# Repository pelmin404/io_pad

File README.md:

# io_pad
A macropad that can act as a push button hub

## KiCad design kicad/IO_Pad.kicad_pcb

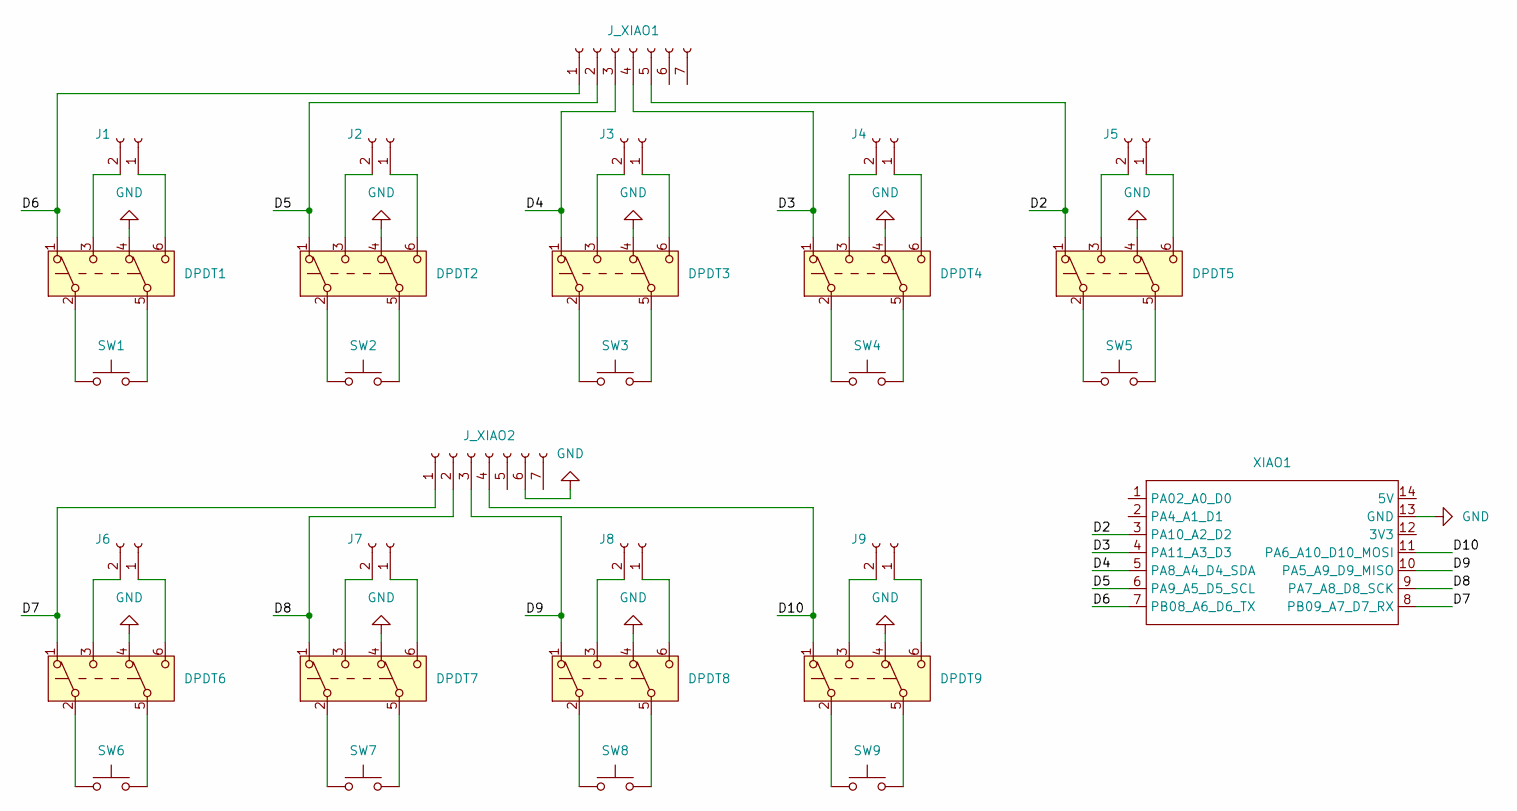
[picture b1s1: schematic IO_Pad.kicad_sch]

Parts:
DPDT1, DPDT2, DPDT3, DPDT4, DPDT5, DPDT6, DPDT7, DPDT8, DPDT9: SW_Push_DPDT; SWITCH_011CQN
J1, J2, J3, J4, J5, J6, J7, J8, J9: Conn_01x02_Socket; PinSocket_1x02_P2.54mm_Vertical
J_XIAO1, J_XIAO2: Conn_01x07_Socket; PinSocket_1x07_P2.54mm_Vertical
SW1, SW2, SW3, SW4, SW5, SW6, SW7, SW8, SW9: SW_Push; MX-Solderable-1U
XIAO1: MOUDLE-SEEEDUINO-XIAO

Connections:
/D2: DPDT5.1 (A), J_XIAO1.5, XIAO1.3 (PA10_A2_D2)
/D3: DPDT4.1 (A), J_XIAO1.4, XIAO1.4 (PA11_A3_D3)
/D4: DPDT3.1 (A), J_XIAO1.3, XIAO1.5 (PA8_A4_D4_SDA)
/D5: DPDT2.1 (A), J_XIAO1.2, XIAO1.6 (PA9_A5_D5_SCL)
/D6: DPDT1.1 (A), J_XIAO1.1, XIAO1.7 (PB08_A6_D6_TX)
/D7: DPDT6.1 (A), J_XIAO2.1, XIAO1.8 (PB09_A7_D7_RX)
/D8: DPDT7.1 (A), J_XIAO2.2, XIAO1.9 (PA7_A8_D8_SCK)
/D9: DPDT8.1 (A), J_XIAO2.3, XIAO1.10 (PA5_A9_D9_MISO)
/D10: DPDT9.1 (A), J_XIAO2.4, XIAO1.11 (PA6_A10_D10_MOSI)
GND: DPDT1.4 (A), DPDT2.4 (A), DPDT3.4 (A), DPDT4.4 (A), DPDT5.4 (A), DPDT6.4 (A), DPDT7.4 (A), DPDT8.4 (A), DPDT9.4 (A), J_XIAO2.6, XIAO1.13 (GND)
unnamed: DPDT1.2 (B), SW1.1
unnamed: DPDT1.5 (B), SW1.2
unnamed: DPDT2.2 (B), SW2.1
unnamed: DPDT2.5 (B), SW2.2
unnamed: DPDT3.2 (B), SW3.1
unnamed: DPDT3.5 (B), SW3.2
unnamed: DPDT4.2 (B), SW4.1
unnamed: DPDT4.5 (B), SW4.2
unnamed: DPDT5.2 (B), SW5.1
unnamed: DPDT5.5 (B), SW5.2
unnamed: DPDT6.2 (B), SW6.1
unnamed: DPDT6.5 (B), SW6.2
unnamed: DPDT7.2 (B), SW7.1
unnamed: DPDT7.5 (B), SW7.2
unnamed: DPDT8.2 (B), SW8.1
unnamed: DPDT8.5 (B), SW8.2
unnamed: DPDT9.2 (B), SW9.1
unnamed: DPDT9.5 (B), SW9.2
unnamed: DPDT1.6 (C), J1.1
unnamed: DPDT1.3 (C), J1.2
unnamed: DPDT2.6 (C), J2.1
unnamed: DPDT2.3 (C), J2.2
unnamed: DPDT3.6 (C), J3.1
unnamed: DPDT3.3 (C), J3.2
unnamed: DPDT4.6 (C), J4.1
unnamed: DPDT4.3 (C), J4.2
unnamed: DPDT5.6 (C), J5.1
unnamed: DPDT5.3 (C), J5.2
unnamed: DPDT6.6 (C), J6.1
unnamed: DPDT6.3 (C), J6.2
unnamed: DPDT7.6 (C), J7.1
unnamed: DPDT7.3 (C), J7.2
unnamed: DPDT8.6 (C), J8.1
unnamed: DPDT8.3 (C), J8.2
unnamed: DPDT9.6 (C), J9.1
unnamed: DPDT9.3 (C), J9.2

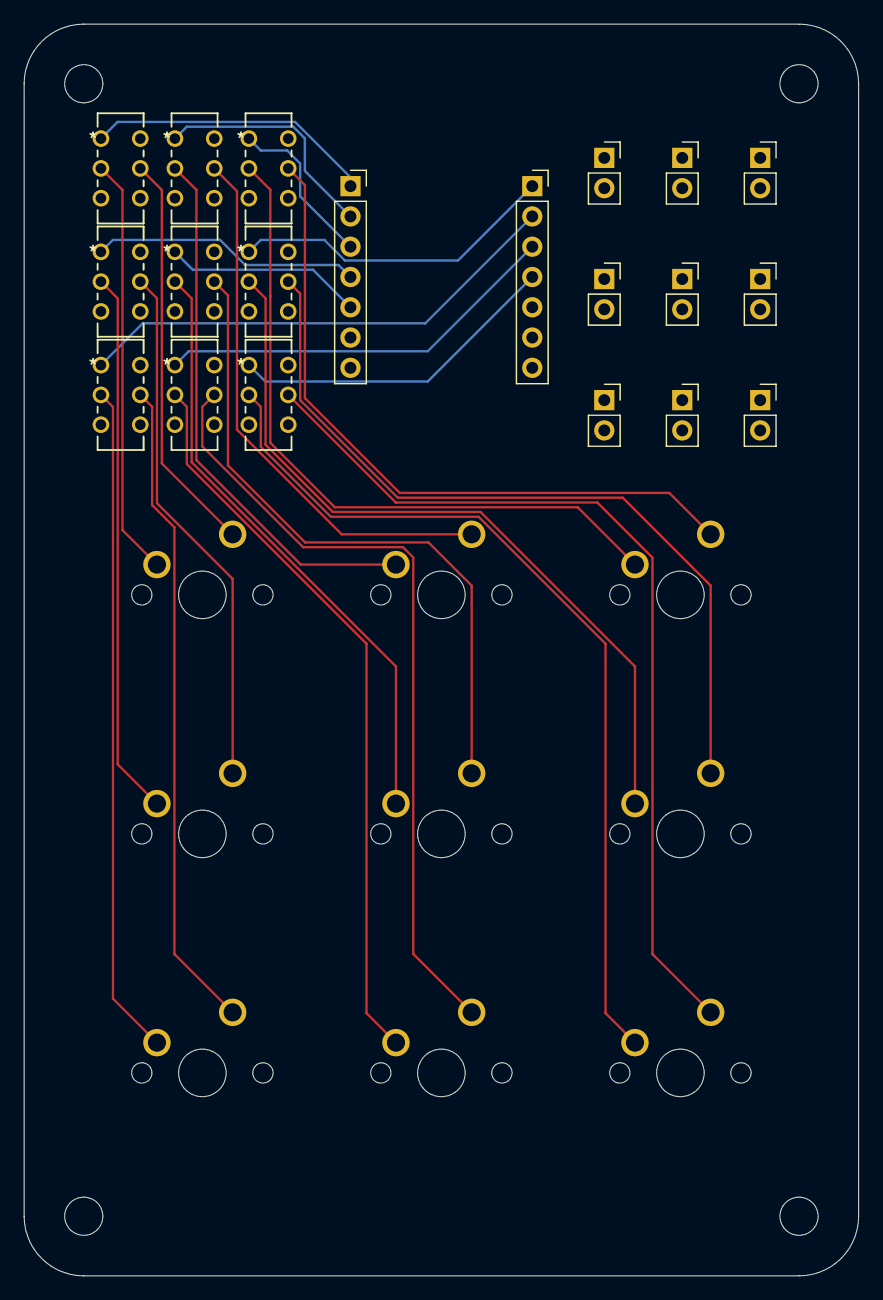
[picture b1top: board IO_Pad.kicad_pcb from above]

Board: 4 copper layers, 70.0 x 105.0 mm, 29 parts (0 on the bottom side), 46 nets.
